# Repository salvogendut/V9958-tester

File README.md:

# V9958 Pico Functional Tester

This is an all-through-hole carrier board that performs a behavioral test of a socketed Yamaha V9958 video display processor. An original RP2040 Raspberry Pi Pico controls the VDP, tests its dedicated 128 KiB VRAM, measures its clocks and analog RGB outputs, and reports the result on green/red LEDs, USB serial, and an on-screen message through an Omega-compatible DIN RGB output.

The current design is **revision 0.3, an unbuilt prototype**. It passes KiCad ERC, DRC, connectivity, and schematic/PCB parity checks, but it still needs physical assembly and calibration before it should be treated as a proven fixture.

## Board mockups

Isometric KiCad 3D rendering of the assembled all-THT carrier board. The custom V9958 socket footprint is shown in the center; the four VRAM sockets are along the upper edge, the DIN RGB socket is at the upper-right edge, and the Pico USB connector projects at the right edge for unobstructed cable access.

Orthographic top rendering showing component placement, test points, socket orientation, controls, and front silkscreen.

## Revision B family and video daughterboard

Revision B separates the functional tester from the optional monitor output. The
[Revision B core](revision-b/) keeps the V9958, four 41464 VRAMs, one
SN74LVC245 data transceiver, one SN74LVC244 monitor buffer, the oscillator,
power integrity, RGB loads and Pico. The Pico drives the V9958 control inputs
directly through 330-ohm series resistors. The CXA1645 and DIN connector have
moved to a separate [RGB DIN daughterboard](video-daughterboard/).

The experimental [Revision B2 SRAM board](revision-b2-sram/) replaces the four
41464 DRAMs with one AS6C1008-55PCN 128Kx8 SRAM, an SN74AHCT573 row-address
latch and an SN74AHCT08 CAS-to-output-enable gate. The Pico still controls and
tests the V9958; it does not emulate the timing-critical video RAM bus.

B2 is smaller at 160 x 110 mm and remains entirely through-hole. It includes
dedicated `/RAS`, `/CAS0`, `/CAS1`, SRAM `/OE` and SRAM `/WE` test points. Its
static KiCad checks pass, but its narrow SRAM timing margin has not been
qualified on hardware. Do not use an unqualified B2 fixture to reject a V9958;
confirm failures on the DRAM-based Revision B or a working Omega.

The two boards use a keyed, straight-through 2x3 IDC cable: pin 1 GND, pin 2
+5 V, pin 3 red, pin 4 green, pin 5 blue and pin 6 composite sync. Revision B
passes or fails without the daughterboard; connect it only when an Omega-style
15.6 kHz RGB monitor output and on-screen result are wanted. Both designs are
unbuilt prototypes and have their own BOM, schematic PDF, validation record,
assembly drawing and Gerber archive.

## What it tests

- CPU bus operation through 3.3 V/5 V level translation.
- V9958 identification field in status register 1. A V9938 should fail this check.
- Two full address-dependent passes over 128 KiB of local VRAM.
- Approximately 3.58 MHz CPUCLK and 15.6 kHz HSYNC/CSYNC.
- Vertical-blank interrupt assertion and status acknowledgement.
- Red, green, and blue analog-channel response through loaded, divided ADC inputs.

A green LED means all behavioral checks passed. A red LED means at least one check failed; USB serial gives the stage and measurements. A pass is **not forensic proof** that the package was manufactured by Yamaha. A sufficiently compatible clone could pass.

The firmware also leaves a 40-column PAL result screen visible on the DIN RGB output. It shows `PASS` or `FAIL`, the numeric stage code, and the failed subsystem. This gives the V9958 a real display-generation test rather than testing only static RGB levels.

## Construction

The tester PCB itself uses no SMD parts. Fit the Pico on two 1x20 through-hole socket strips; the Pico module is, of course, an already assembled module containing SMD components. Use sockets for U1–U9 and especially the V9958 DUT.

Important parts:

- U3 footprint: custom SDIP-64, 1.778 mm pin pitch, 19.05 mm row spacing.
- U5–U8: four 41464-compatible 64Kx4 DRAMs, 120 ns or faster.
- U1: SN74LVC245AN, powered from 3.3 V.
- U2: SN74AHCT244N, powered from 5 V.
- U4: SN74LVC244AN, powered from 3.3 V.
- U9: CXA1645P in DIP-24, used as the three-channel 75-ohm RGB cable buffer.
- J1: Omega-compatible 8-pin DIN RGB socket using the original Omega footprint and pin numbering.
- Y1: 21.477270 MHz crystal; C1 is the 30 pF oscillator trimmer.
- F1: Bourns MF-RHT100 resettable fuse, 1.0 A hold / 1.8 A trip.

The grouped [BOM](docs/BOM.csv), [schematic PDF](docs/V9958-Tester-Schematic.pdf), and [test procedure](docs/TEST-PROCEDURE.md) are in `docs/`. Gerbers and drill files are in `fabrication/` after running the release export.

## Power and handling

Power the board only through the Pico USB connector, from a good 5 V supply capable of at least 1 A. For first power-up, use a current-limited bench supply or USB power limiter. Never insert or remove the V9958, VRAM, logic chips, or Pico while powered.

The board provides native 15.6 kHz PAL RGB through J1. It is suitable for an Omega/MSX RGB cable and a compatible RGB monitor or SCART input; it is **not 31 kHz VGA** and must not be connected to a VGA-only display. J1 follows the Omega assignments: pin 1 ground, pin 3 AV control, pin 4 attenuated composite sync, pin 5 RGB/YS control, pin 6 red, pin 7 green, and pin 8 blue. Pin 2 (audio on an Omega) is unconnected because the tester has no audio source.

U9 reproduces the Omega-style buffered RGB path: 0.1 uF input coupling, CXA1645 clamping/drivers, and 75 ohm plus 220 uF output coupling per colour. J1 pin 4 carries sync only, not composite video. Scope points remain available for 5 V, 3.3 V, ground, CPUCLK, HSYNC, CSYNC, and raw R/G/B.

## Firmware

Firmware source is in `firmware/`. With a Pico SDK toolchain installed:

```sh
export PICO_SDK_PATH=/path/to/pico-sdk
cmake -S firmware -B firmware/build -DPICO_BOARD=pico
cmake --build firmware/build -j4
```

Copy `v9958_tester.uf2` to a Pico in BOOTSEL mode. The program runs once at power-up and again whenever SW1 is pressed. USB CDC serial prints the clock counts, VDP ID, first VRAM mismatch if any, interrupt result, RGB ADC readings, and final stage code. At completion it programs V9958 PAL text mode and shows the same result through J1.

Revision B and B2 use the same source with separate builds in
`revision-b/firmware/` and `revision-b2-sram/firmware/`. They have no TEST
button; send `R` over USB serial to repeat the test.

## Design files and regeneration

- `V9958-Tester.kicad_sch`: native KiCad 10 schematic.
- `V9958-Tester.kicad_pcb`: two-layer routed board with GND pours.
- `V9958-Tester.kicad_pro`: project settings.
- `V9958-Tester.pretty/`: custom V9958, trimmer, and Omega DIN-8 footprints.
- `tools/`: deterministic schematic, footprint, placement, finish, and BOM generators.

The routing was completed with Freerouting and then imported and checked by KiCad. The checked-in PCB is the release artifact; rerunning the placement generator intentionally produces an unrouted board.

## Known prototype limitations

- RGB pass thresholds are conservative defaults and must be calibrated on known-good V9958 samples.
- The full VRAM test and VDP port timing must be verified on physical hardware.
- Socket/ZIF mechanical fit must be checked against the exact part you intend to buy.
- CXA1645 RGB amplitude, sync attenuation, DIN socket fit, and compatibility with the intended Omega RGB cable must be confirmed on the first prototype.
- The test identifies behavior, not die markings or provenance.

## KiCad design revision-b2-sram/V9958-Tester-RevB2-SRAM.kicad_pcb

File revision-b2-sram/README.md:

# V9958 Tester Revision B2 SRAM

Revision B2 is an experimental all-through-hole variant of the V9958 tester.
It replaces Revision B's four 41464 DRAMs with one AS6C1008-55PCN 128Kx8
asynchronous SRAM, one SN74AHCT573N row-address latch and one SN74AHCT08N
CAS-to-output-enable gate. The Pico still performs the test; it does not
emulate cycle-accurate video RAM.

The V9958 presents each memory address in two halves. U6 captures the row
address when `/RAS` falls. The live address becomes SRAM A0-A7, the latched
row becomes A8-A15, and `/CAS0` becomes A16. U7 asserts SRAM `/OE` when either
`/CAS0` or `/CAS1` is active. SRAM `/CE` is held low and V9958 `R/W` drives
SRAM `/WE` through a 47-ohm damping resistor.

This adaptation is intentionally marked **EXPERIMENTAL PROTOTYPE**. Static
ERC/DRC and connectivity checks cannot prove that the SRAM interface meets
the V9958's dynamic memory timing. Before trusting it as a chip tester, build
one unit and qualify TP8-TP12 with a known-good V9958 over supply and
temperature. Do not substitute slower SRAM.

J1 has the same keyed 2x3 video expansion pinout as Revision B: 1 GND, 2 +5 V,
3 red, 4 green, 5 blue and 6 CSYNC. It works with the existing optional RGB
DIN daughterboard.

The grouped [BOM](docs/BOM.csv), [schematic PDF](docs/V9958-Tester-RevB2-SRAM-Schematic.pdf),
[test procedure](docs/TEST-PROCEDURE.md), [design notes](docs/DESIGN-NOTES.md)
and [validation record](docs/VALIDATION.md) are included.

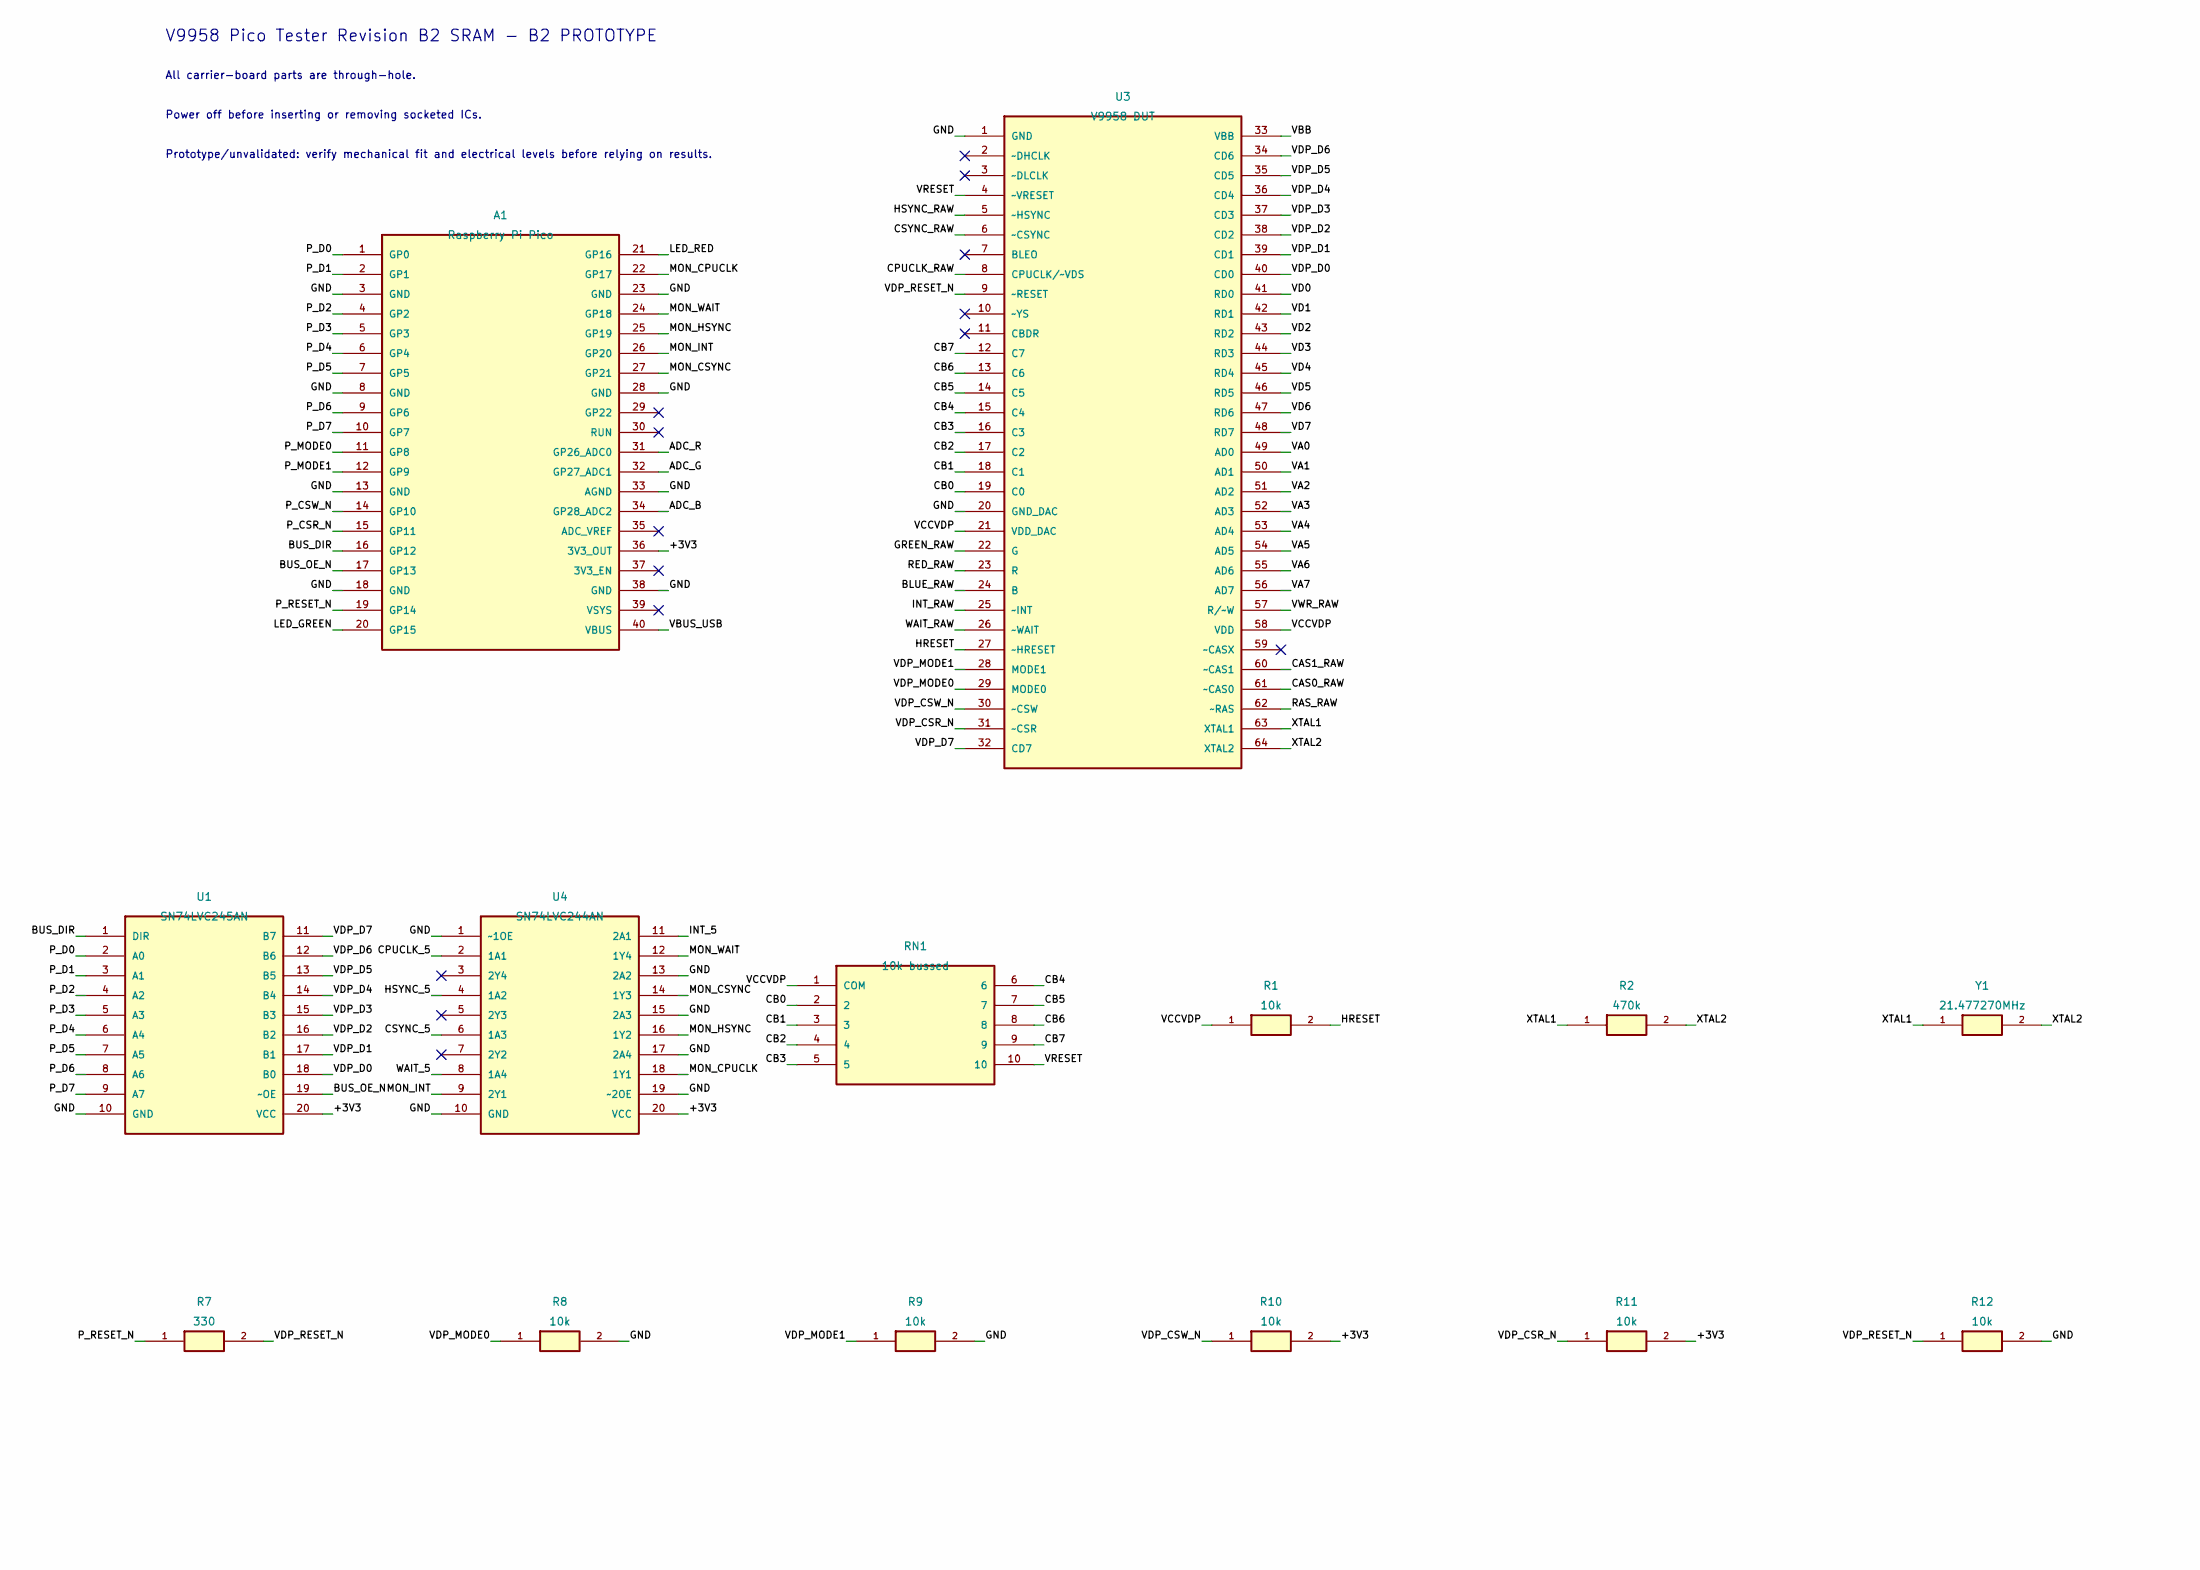
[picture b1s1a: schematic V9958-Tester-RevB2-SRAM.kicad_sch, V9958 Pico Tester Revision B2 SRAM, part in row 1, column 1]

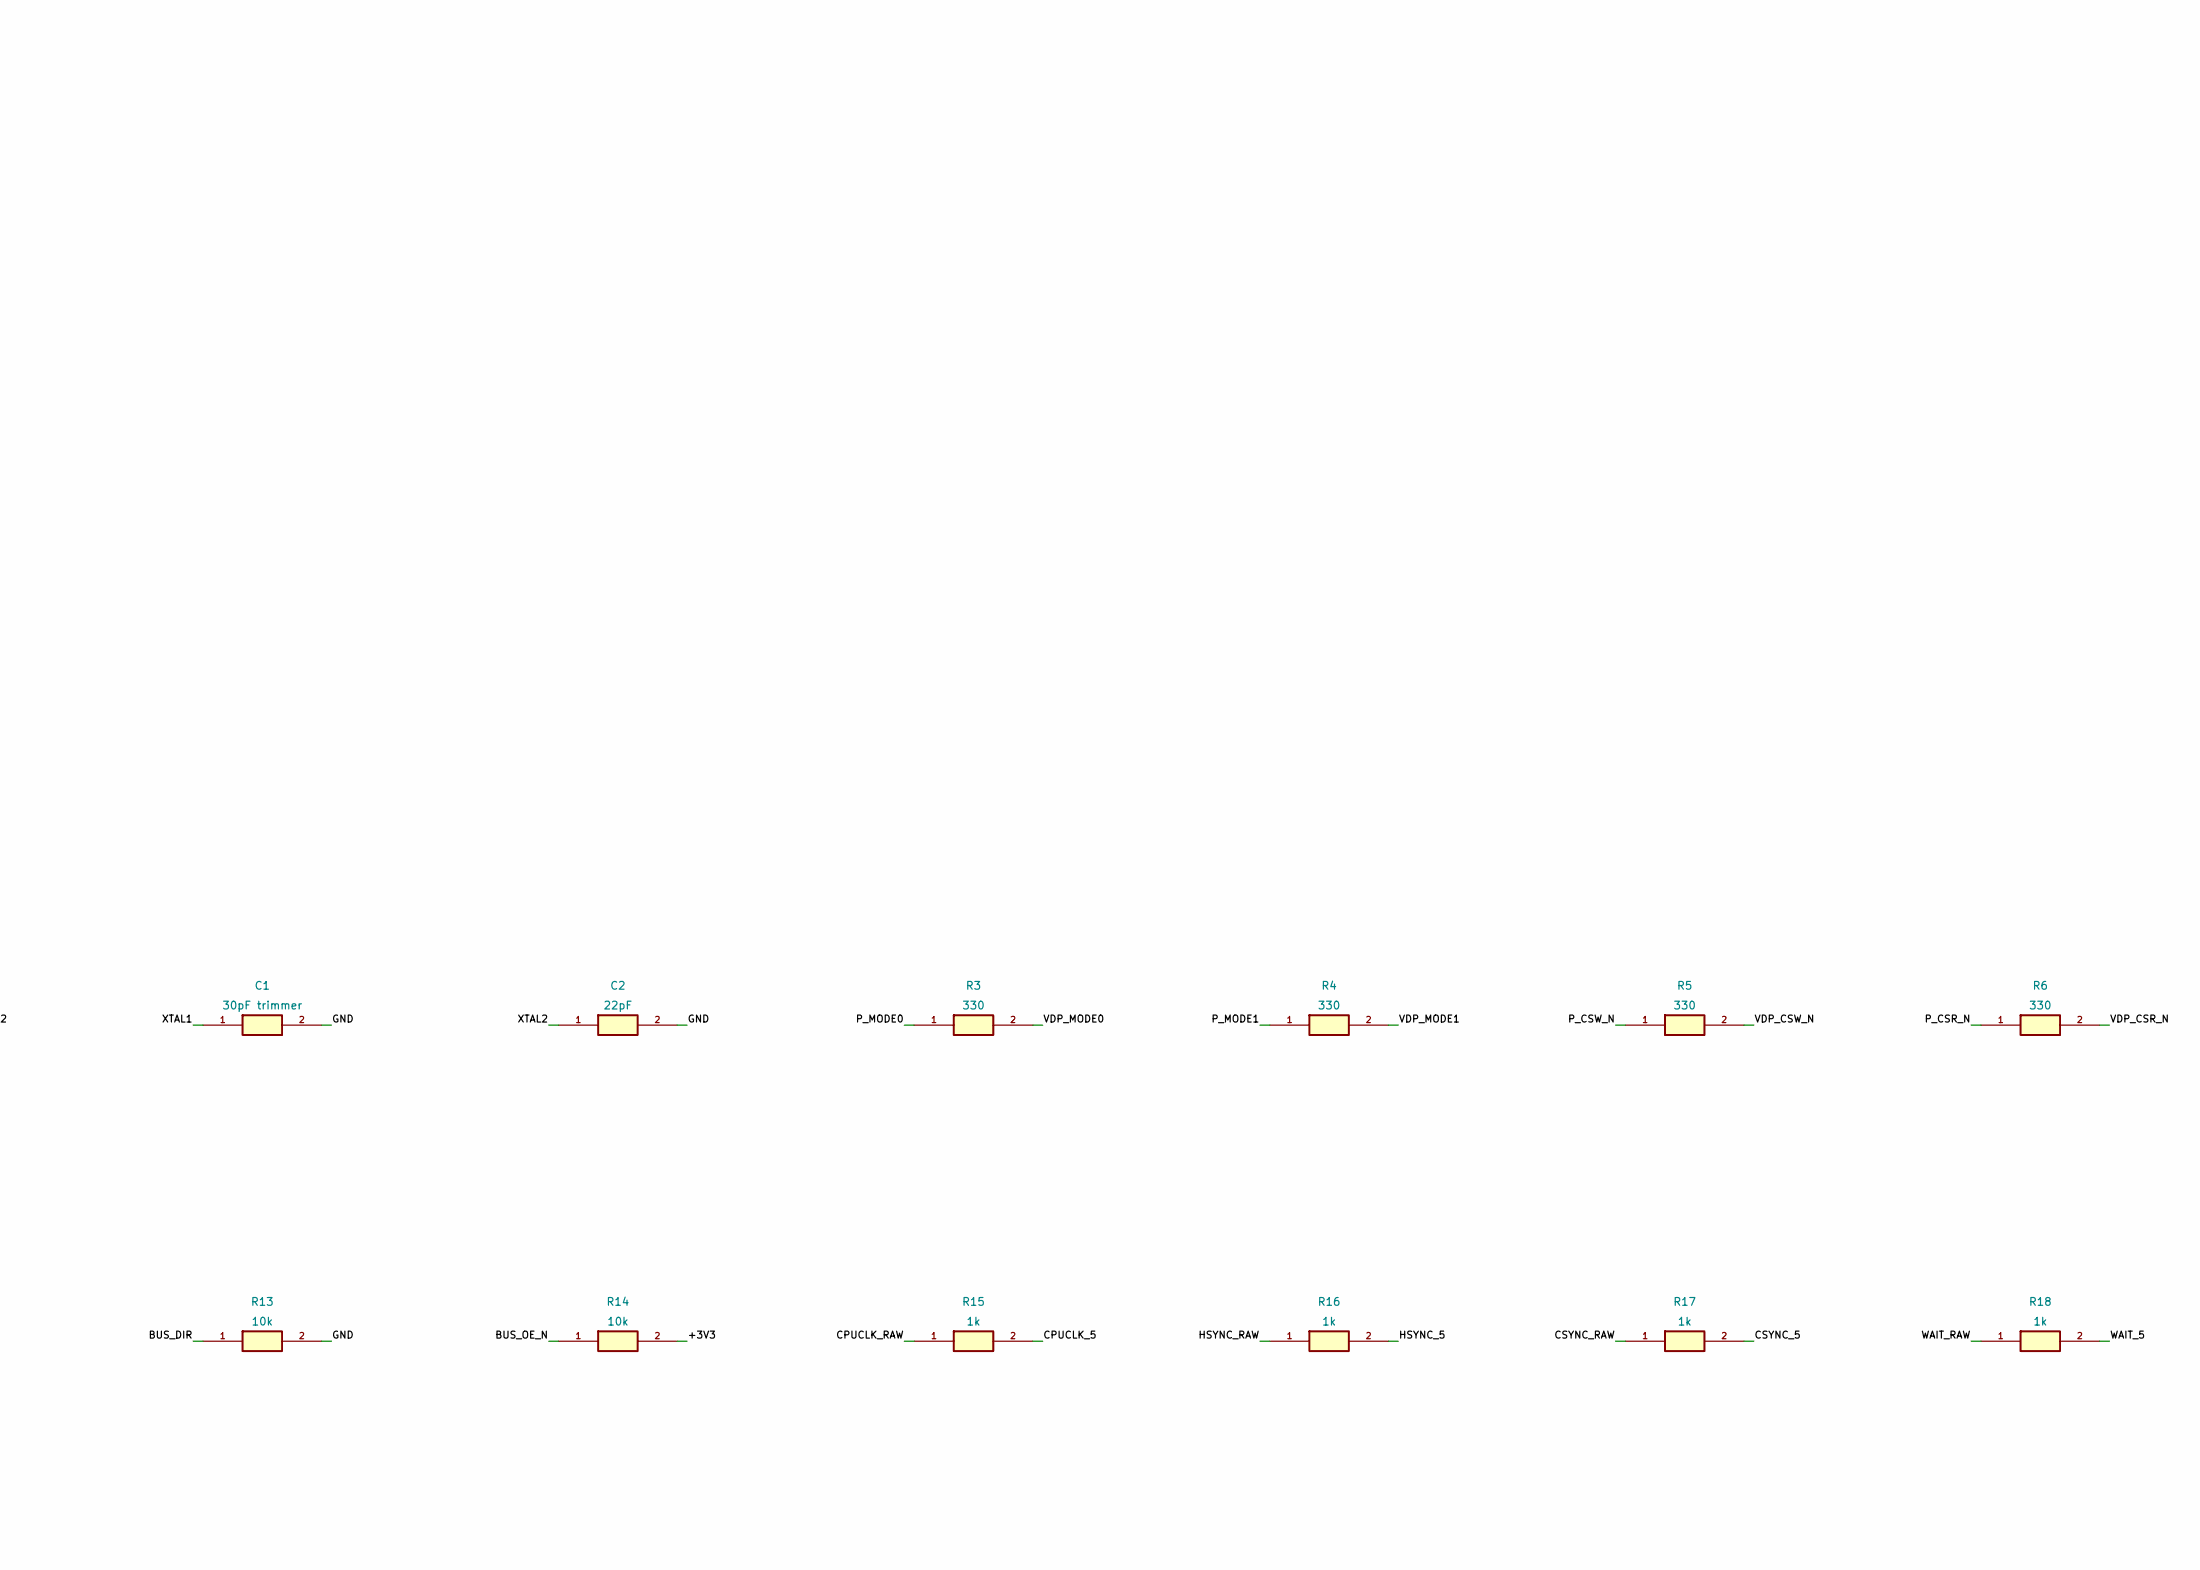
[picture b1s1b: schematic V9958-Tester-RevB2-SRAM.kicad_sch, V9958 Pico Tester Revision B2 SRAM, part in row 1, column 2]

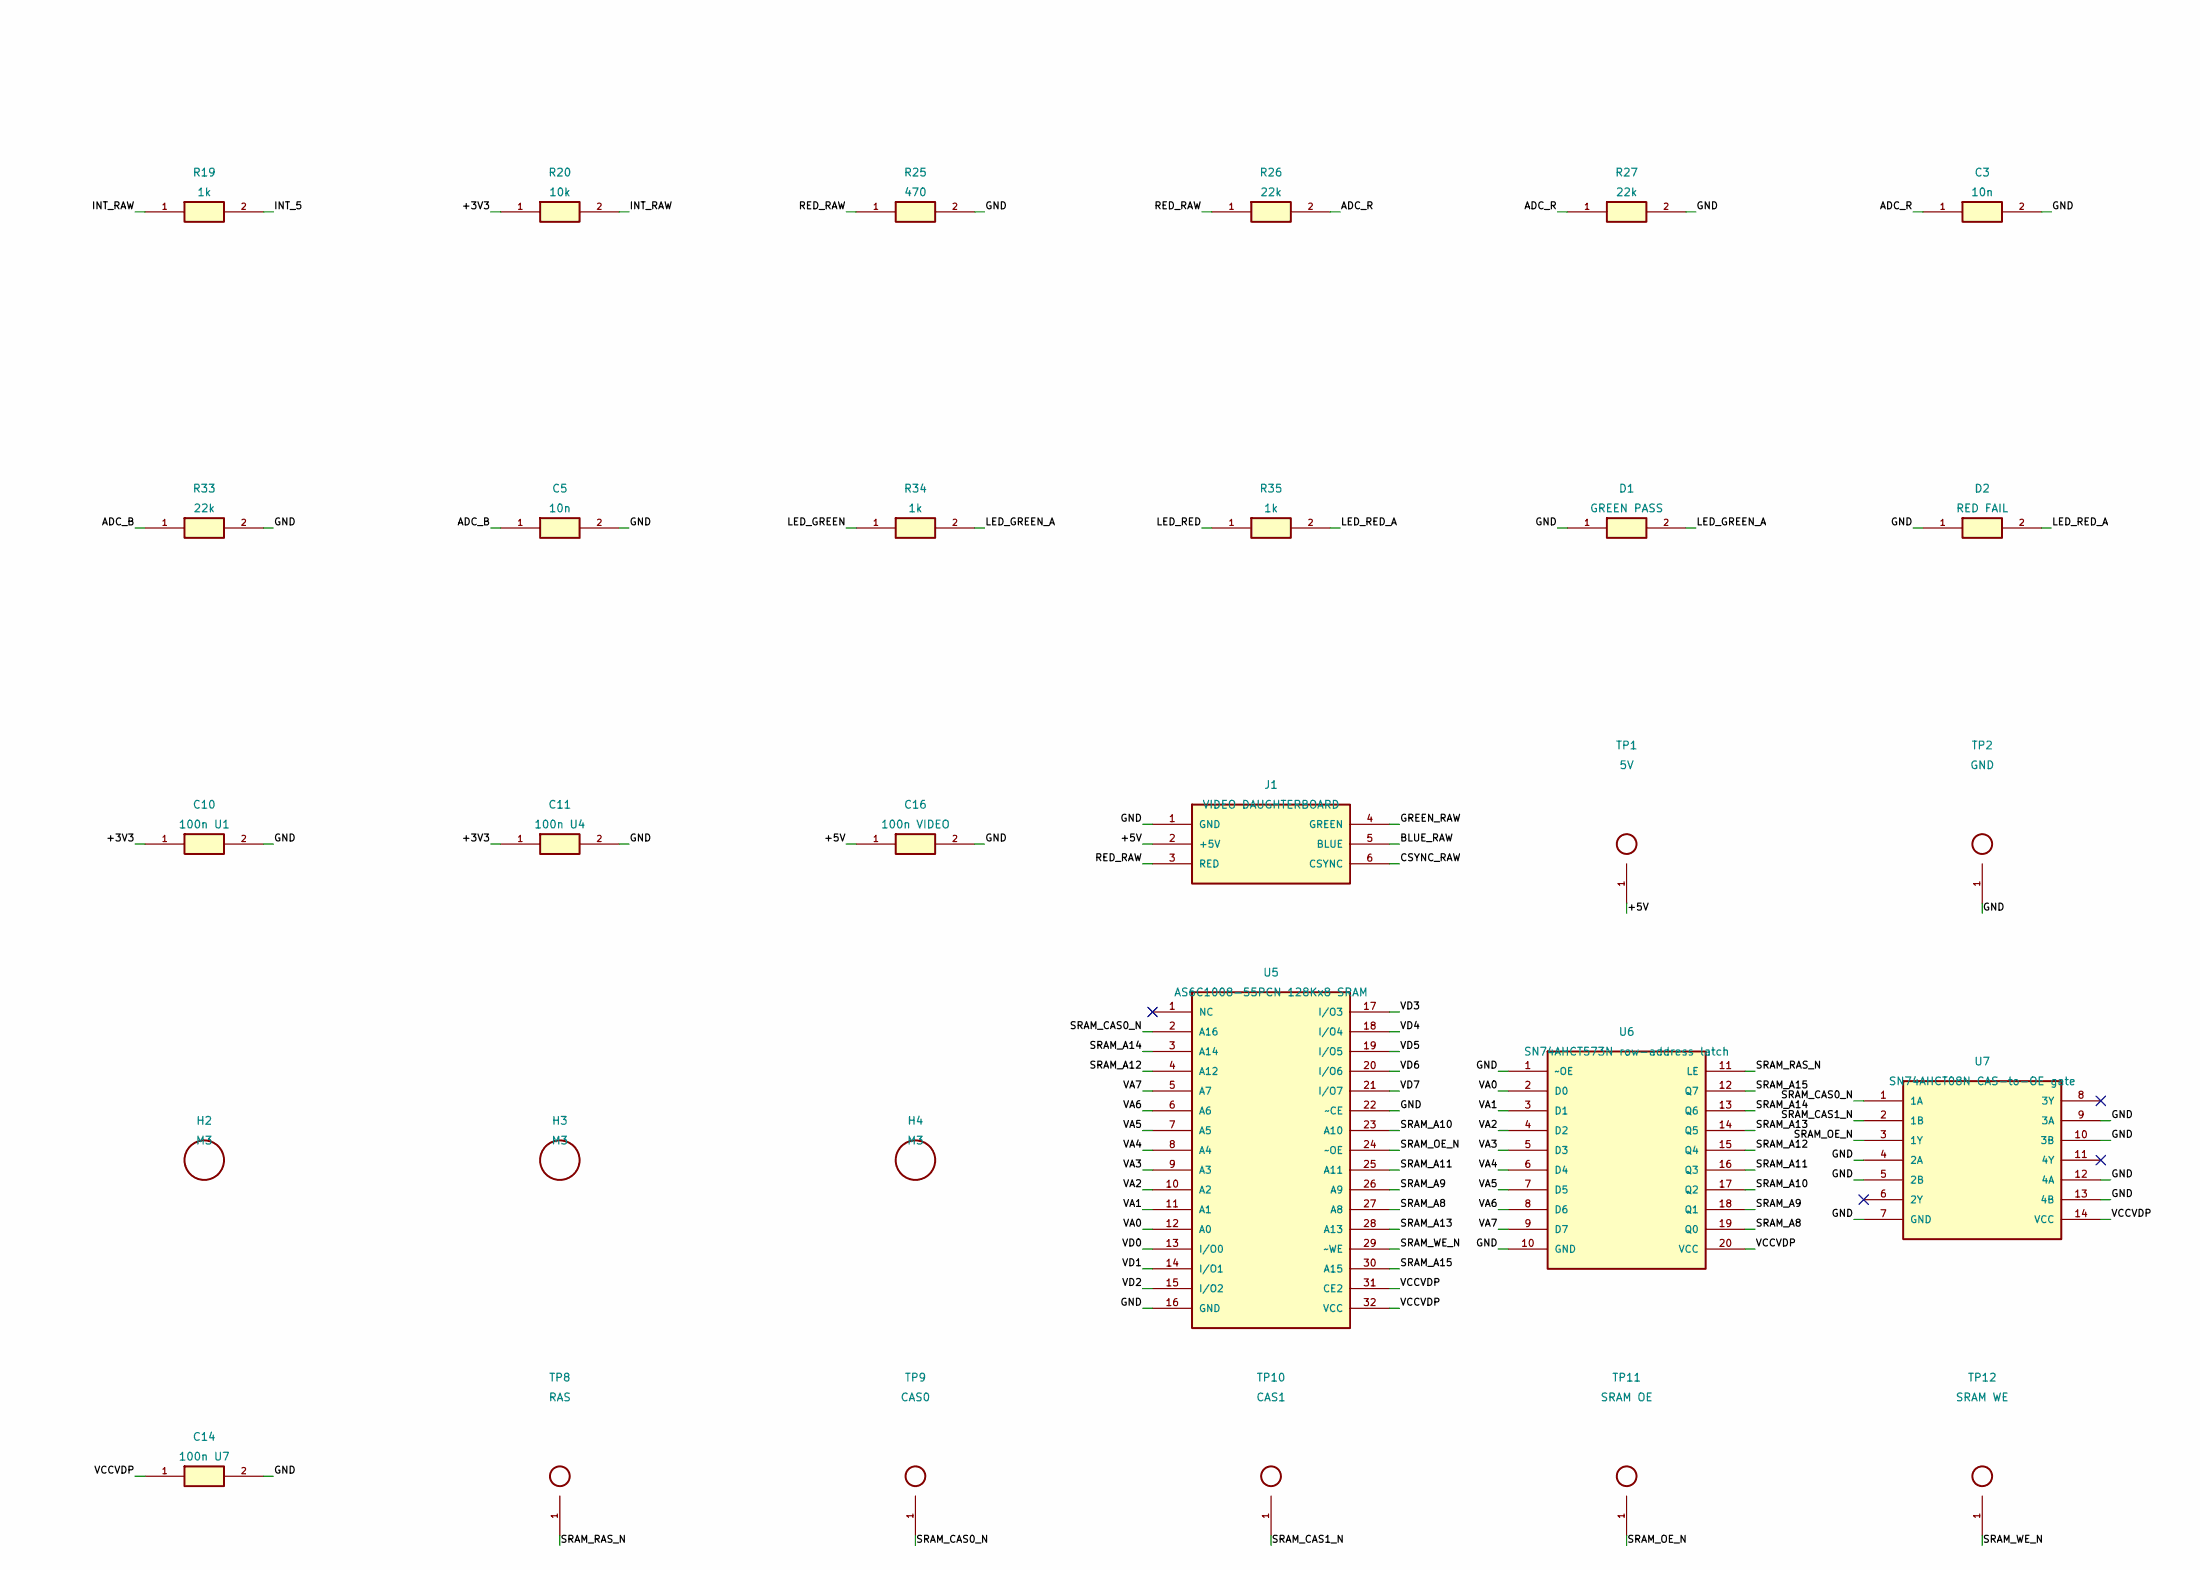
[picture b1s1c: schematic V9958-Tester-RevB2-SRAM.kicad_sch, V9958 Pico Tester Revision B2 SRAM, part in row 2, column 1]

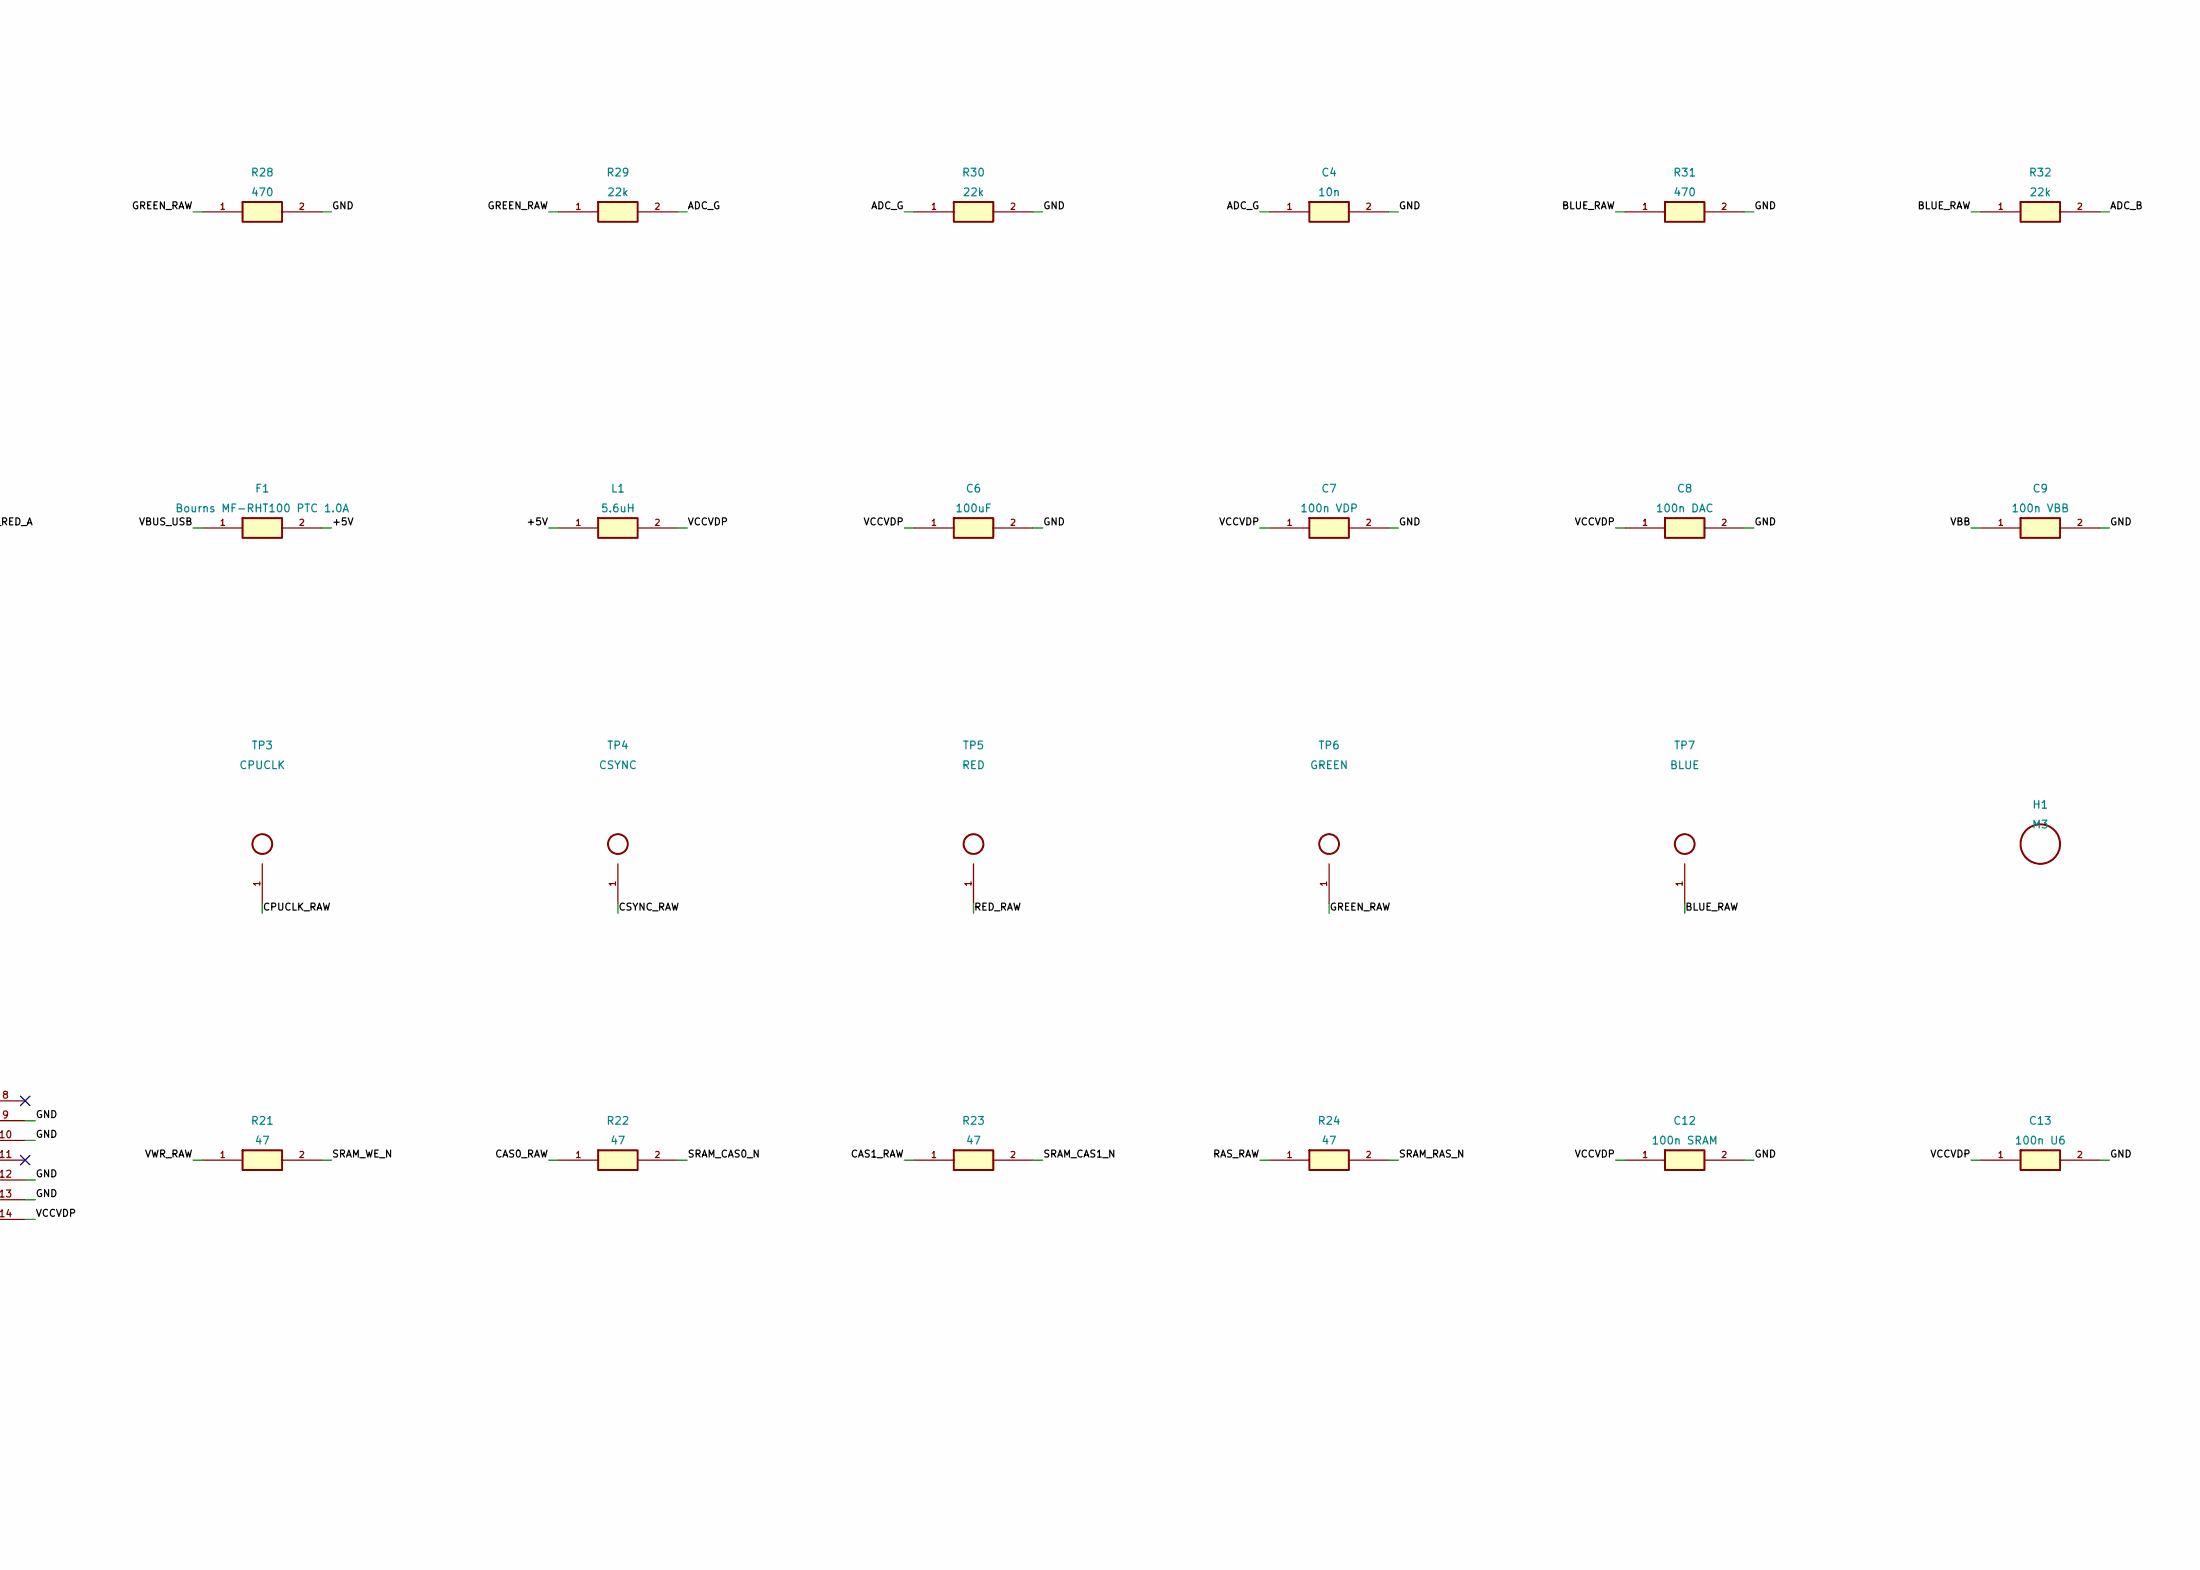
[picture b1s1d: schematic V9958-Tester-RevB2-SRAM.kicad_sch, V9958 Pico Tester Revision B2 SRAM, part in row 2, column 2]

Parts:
A1: Raspberry Pi Pico; RaspberryPi_Pico_Common_THT
C1: 30pF trimmer; C_Trim_P5.00mm
C2: 22pF; C_Disc_D5.0mm_W2.5mm_P5.00mm
C3, C4, C5: 10n; C_Disc_D5.0mm_W2.5mm_P5.00mm
C6: 100uF; CP_Radial_D5.0mm_P2.00mm
C7: 100n VDP; C_Disc_D5.0mm_W2.5mm_P5.00mm
C8: 100n DAC; C_Disc_D5.0mm_W2.5mm_P5.00mm
C9: 100n VBB; C_Disc_D5.0mm_W2.5mm_P5.00mm
C10: 100n U1; C_Disc_D5.0mm_W2.5mm_P5.00mm
C11: 100n U4; C_Disc_D5.0mm_W2.5mm_P5.00mm
C12: 100n SRAM; C_Disc_D5.0mm_W2.5mm_P5.00mm
C13: 100n U6; C_Disc_D5.0mm_W2.5mm_P5.00mm
C14: 100n U7; C_Disc_D5.0mm_W2.5mm_P5.00mm
C16: 100n VIDEO; C_Disc_D5.0mm_W2.5mm_P5.00mm
D1: GREEN PASS; LED_D5.0mm
D2: RED FAIL; LED_D5.0mm
F1: Bourns MF-RHT100 PTC 1.0A; Fuse_Bourns_MF-RHT100
H1, H2, H3, H4: M3; MountingHole_3.2mm_M3
J1: VIDEO DAUGHTERBOARD; IDC-Header_2x03_P2.54mm_Vertical
L1: 5.6uH; L_Axial_L14.0mm_D4.5mm_P15.24mm_Horizontal_Fastron_LACC
R1, R8, R9, R10, R11, R12, R13, R14, R20: 10k; R_Axial_DIN0207_L6.3mm_D2.5mm_P7.62mm_Horizontal
R2: 470k; R_Axial_DIN0207_L6.3mm_D2.5mm_P7.62mm_Horizontal
R3, R4, R5, R6, R7: 330; R_Axial_DIN0207_L6.3mm_D2.5mm_P7.62mm_Horizontal
R15, R16, R17, R18, R19, R34, R35: 1k; R_Axial_DIN0207_L6.3mm_D2.5mm_P7.62mm_Horizontal
R21, R22, R23, R24: 47; R_Axial_DIN0207_L6.3mm_D2.5mm_P7.62mm_Horizontal
R25, R28, R31: 470; R_Axial_DIN0207_L6.3mm_D2.5mm_P7.62mm_Horizontal
R26, R27, R29, R30, R32, R33: 22k; R_Axial_DIN0207_L6.3mm_D2.5mm_P7.62mm_Horizontal
RN1: 10k bussed; R_Array_SIP10
TP1: 5V; TestPoint_THTPad_D2.0mm_Drill1.0mm
TP2: GND; TestPoint_THTPad_D2.0mm_Drill1.0mm
TP3: CPUCLK; TestPoint_THTPad_D2.0mm_Drill1.0mm
TP4: CSYNC; TestPoint_THTPad_D2.0mm_Drill1.0mm
TP5: RED; TestPoint_THTPad_D2.0mm_Drill1.0mm
TP6: GREEN; TestPoint_THTPad_D2.0mm_Drill1.0mm
TP7: BLUE; TestPoint_THTPad_D2.0mm_Drill1.0mm
TP8: RAS; TestPoint_THTPad_D2.0mm_Drill1.0mm
TP9: CAS0; TestPoint_THTPad_D2.0mm_Drill1.0mm
TP10: CAS1; TestPoint_THTPad_D2.0mm_Drill1.0mm
TP11: SRAM OE; TestPoint_THTPad_D2.0mm_Drill1.0mm
TP12: SRAM WE; TestPoint_THTPad_D2.0mm_Drill1.0mm
U1: SN74LVC245AN; DIP-20_W7.62mm_Socket_LongPads
U3: V9958 DUT; SDIP-64_W19.05mm_P1.778mm_Socket
U4: SN74LVC244AN; DIP-20_W7.62mm_Socket_LongPads
U5: AS6C1008-55PCN 128Kx8 SRAM; DIP-32_W15.24mm_Socket_LongPads
U6: SN74AHCT573N row-address latch; DIP-20_W7.62mm_Socket_LongPads
U7: SN74AHCT08N CAS-to-OE gate; DIP-14_W7.62mm_Socket_LongPads
Y1: 21.477270MHz; Crystal_HC49-U_Vertical

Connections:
/+3V3: A1.36 (3V3_OUT), C10.1, C11.1, R10.2, R11.2, R14.2, R20.1, U1.20 (VCC), U4.20 (VCC)
/+5V: C16.1, F1.2, J1.2 (+5V), L1.1, TP1.1
/ADC_B: A1.34 (GP28_ADC2), C5.1, R32.2, R33.1
/ADC_G: A1.32 (GP27_ADC1), C4.1, R29.2, R30.1
/ADC_R: A1.31 (GP26_ADC0), C3.1, R26.2, R27.1
/BLUE_RAW: J1.5 (BLUE), R31.1, R32.1, TP7.1, U3.24 (B)
/BUS_DIR: A1.16 (GP12), R13.1, U1.1 (DIR)
/BUS_OE_N: A1.17 (GP13), R14.1, U1.19 (~OE)
/CAS0_RAW: R22.1, U3.61 (~CAS0)
/CAS1_RAW: R23.1, U3.60 (~CAS1)
/CB0: RN1.2, U3.19 (C0)
/CB1: RN1.3, U3.18 (C1)
/CB2: RN1.4, U3.17 (C2)
/CB3: RN1.5, U3.16 (C3)
/CB4: RN1.6, U3.15 (C4)
/CB5: RN1.7, U3.14 (C5)
/CB6: RN1.8, U3.13 (C6)
/CB7: RN1.9, U3.12 (C7)
/CPUCLK_5: R15.2, U4.2 (1A1)
/CPUCLK_RAW: R15.1, TP3.1, U3.8 (CPUCLK/~VDS)
/CSYNC_5: R17.2, U4.6 (1A3)
/CSYNC_RAW: J1.6 (CSYNC), R17.1, TP4.1, U3.6 (~CSYNC)
/GND: A1.3 (GND), A1.8 (GND), A1.13 (GND), A1.18 (GND), A1.23 (GND), A1.28 (GND), A1.33 (AGND), A1.38 (GND), C1.2, C2.2, C3.2, C4.2, C5.2, C6.2, C7.2, C8.2, C9.2, C10.2, C11.2, C12.2, C13.2, C14.2, C16.2, D1.1, D2.1, J1.1 (GND), R8.2, R9.2, R12.2, R13.2, R25.2, R27.2, R28.2, R30.2, R31.2, R33.2, TP2.1, U1.10 (GND), U3.1 (GND), U3.20 (GND_DAC), U4.1 (~1OE), U4.10 (GND), U4.13 (2A2), U4.15 (2A3), U4.17 (2A4), U4.19 (~2OE), U5.16 (GND), U5.22 (~CE), U6.1 (~OE), U6.10 (GND), U7.4 (2A), U7.5 (2B), U7.7 (GND), U7.9 (3A), U7.10 (3B), U7.12 (4A), U7.13 (4B)
/GREEN_RAW: J1.4 (GREEN), R28.1, R29.1, TP6.1, U3.22 (G)
/HRESET: R1.2, U3.27 (~HRESET)
/HSYNC_5: R16.2, U4.4 (1A2)
/HSYNC_RAW: R16.1, U3.5 (~HSYNC)
/INT_5: R19.2, U4.11 (2A1)
/INT_RAW: R19.1, R20.2, U3.25 (~INT)
/LED_GREEN: A1.20 (GP15), R34.1
/LED_GREEN_A: D1.2, R34.2
/LED_RED: A1.21 (GP16), R35.1
/LED_RED_A: D2.2, R35.2
/MON_CPUCLK: A1.22 (GP17), U4.18 (1Y1)
/MON_CSYNC: A1.27 (GP21), U4.14 (1Y3)
/MON_HSYNC: A1.25 (GP19), U4.16 (1Y2)
/MON_INT: A1.26 (GP20), U4.9 (2Y1)
/MON_WAIT: A1.24 (GP18), U4.12 (1Y4)
/P_CSR_N: A1.15 (GP11), R6.1
/P_CSW_N: A1.14 (GP10), R5.1
/P_D0: A1.1 (GP0), U1.2 (A0)
/P_D1: A1.2 (GP1), U1.3 (A1)
/P_D2: A1.4 (GP2), U1.4 (A2)
/P_D3: A1.5 (GP3), U1.5 (A3)
/P_D4: A1.6 (GP4), U1.6 (A4)
/P_D5: A1.7 (GP5), U1.7 (A5)
/P_D6: A1.9 (GP6), U1.8 (A6)
/P_D7: A1.10 (GP7), U1.9 (A7)
/P_MODE0: A1.11 (GP8), R3.1
/P_MODE1: A1.12 (GP9), R4.1
/P_RESET_N: A1.19 (GP14), R7.1
/RAS_RAW: R24.1, U3.62 (~RAS)
/RED_RAW: J1.3 (RED), R25.1, R26.1, TP5.1, U3.23 (R)
/SRAM_A8: U5.27 (A8), U6.19 (Q0)
/SRAM_A9: U5.26 (A9), U6.18 (Q1)
/SRAM_A10: U5.23 (A10), U6.17 (Q2)
/SRAM_A11: U5.25 (A11), U6.16 (Q3)
/SRAM_A12: U5.4 (A12), U6.15 (Q4)
/SRAM_A13: U5.28 (A13), U6.14 (Q5)
/SRAM_A14: U5.3 (A14), U6.13 (Q6)
/SRAM_A15: U5.30 (A15), U6.12 (Q7)
/SRAM_CAS0_N: R22.2, TP9.1, U5.2 (A16), U7.1 (1A)
/SRAM_CAS1_N: R23.2, TP10.1, U7.2 (1B)
/SRAM_OE_N: TP11.1, U5.24 (~OE), U7.3 (1Y)
/SRAM_RAS_N: R24.2, TP8.1, U6.11 (LE)
/SRAM_WE_N: R21.2, TP12.1, U5.29 (~WE)
/VA0: U3.49 (AD0), U5.12 (A0), U6.2 (D0)
/VA1: U3.50 (AD1), U5.11 (A1), U6.3 (D1)
/VA2: U3.51 (AD2), U5.10 (A2), U6.4 (D2)
/VA3: U3.52 (AD3), U5.9 (A3), U6.5 (D3)
/VA4: U3.53 (AD4), U5.8 (A4), U6.6 (D4)
/VA5: U3.54 (AD5), U5.7 (A5), U6.7 (D5)
/VA6: U3.55 (AD6), U5.6 (A6), U6.8 (D6)
/VA7: U3.56 (AD7), U5.5 (A7), U6.9 (D7)
/VBB: C9.1, U3.33 (VBB)
/VBUS_USB: A1.40 (VBUS), F1.1
/VCCVDP: C6.1, C7.1, C8.1, C12.1, C13.1, C14.1, L1.2, R1.1, RN1.1 (COM), U3.21 (VDD_DAC), U3.58 (VDD), U5.31 (CE2), U5.32 (VCC), U6.20 (VCC), U7.14 (VCC)
/VD0: U3.41 (RD0), U5.13 (I/O0)
/VD1: U3.42 (RD1), U5.14 (I/O1)
/VD2: U3.43 (RD2), U5.15 (I/O2)
/VD3: U3.44 (RD3), U5.17 (I/O3)
/VD4: U3.45 (RD4), U5.18 (I/O4)
/VD5: U3.46 (RD5), U5.19 (I/O5)
/VD6: U3.47 (RD6), U5.20 (I/O6)
/VD7: U3.48 (RD7), U5.21 (I/O7)
/VDP_CSR_N: R6.2, R11.1, U3.31 (~CSR)
/VDP_CSW_N: R5.2, R10.1, U3.30 (~CSW)
/VDP_D0: U1.18 (B0), U3.40 (CD0)
/VDP_D1: U1.17 (B1), U3.39 (CD1)
/VDP_D2: U1.16 (B2), U3.38 (CD2)
/VDP_D3: U1.15 (B3), U3.37 (CD3)
/VDP_D4: U1.14 (B4), U3.36 (CD4)
/VDP_D5: U1.13 (B5), U3.35 (CD5)
/VDP_D6: U1.12 (B6), U3.34 (CD6)
/VDP_D7: U1.11 (B7), U3.32 (CD7)
/VDP_MODE0: R3.2, R8.1, U3.29 (MODE0)
/VDP_MODE1: R4.2, R9.1, U3.28 (MODE1)
/VDP_RESET_N: R7.2, R12.1, U3.9 (~RESET)
/VRESET: RN1.10, U3.4 (~VRESET)
/VWR_RAW: R21.1, U3.57 (R/~W)
/WAIT_5: R18.2, U4.8 (1A4)
/WAIT_RAW: R18.1, U3.26 (~WAIT)
/XTAL1: C1.1, R2.1, U3.63 (XTAL1), Y1.1
/XTAL2: C2.1, R2.2, U3.64 (XTAL2), Y1.2

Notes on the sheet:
V9958 Pico Tester Revision B2 SRAM - B2 PROTOTYPE
All carrier-board parts are through-hole.
Power off before inserting or removing socketed ICs.
Prototype/unvalidated: verify mechanical fit and electrical levels before relying on results.
